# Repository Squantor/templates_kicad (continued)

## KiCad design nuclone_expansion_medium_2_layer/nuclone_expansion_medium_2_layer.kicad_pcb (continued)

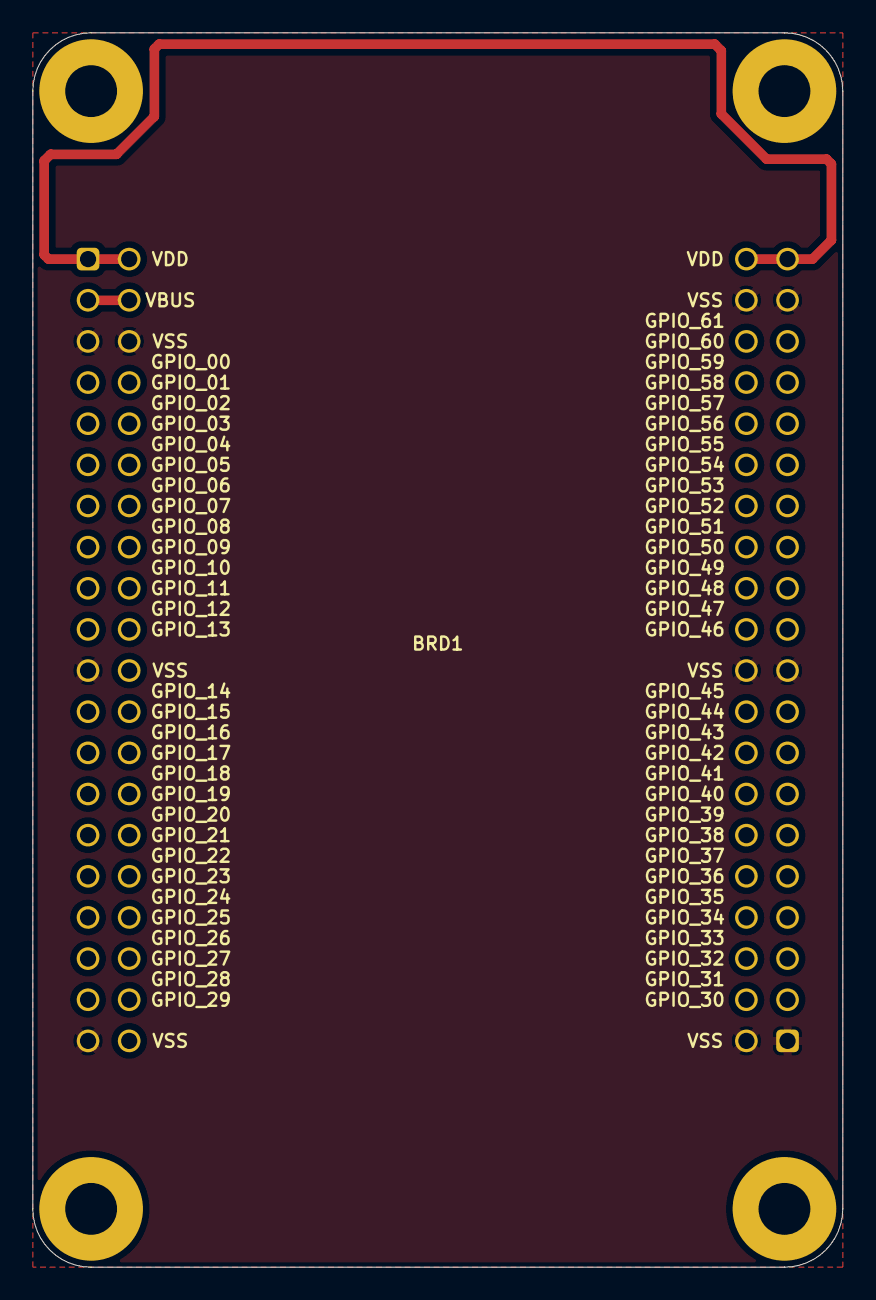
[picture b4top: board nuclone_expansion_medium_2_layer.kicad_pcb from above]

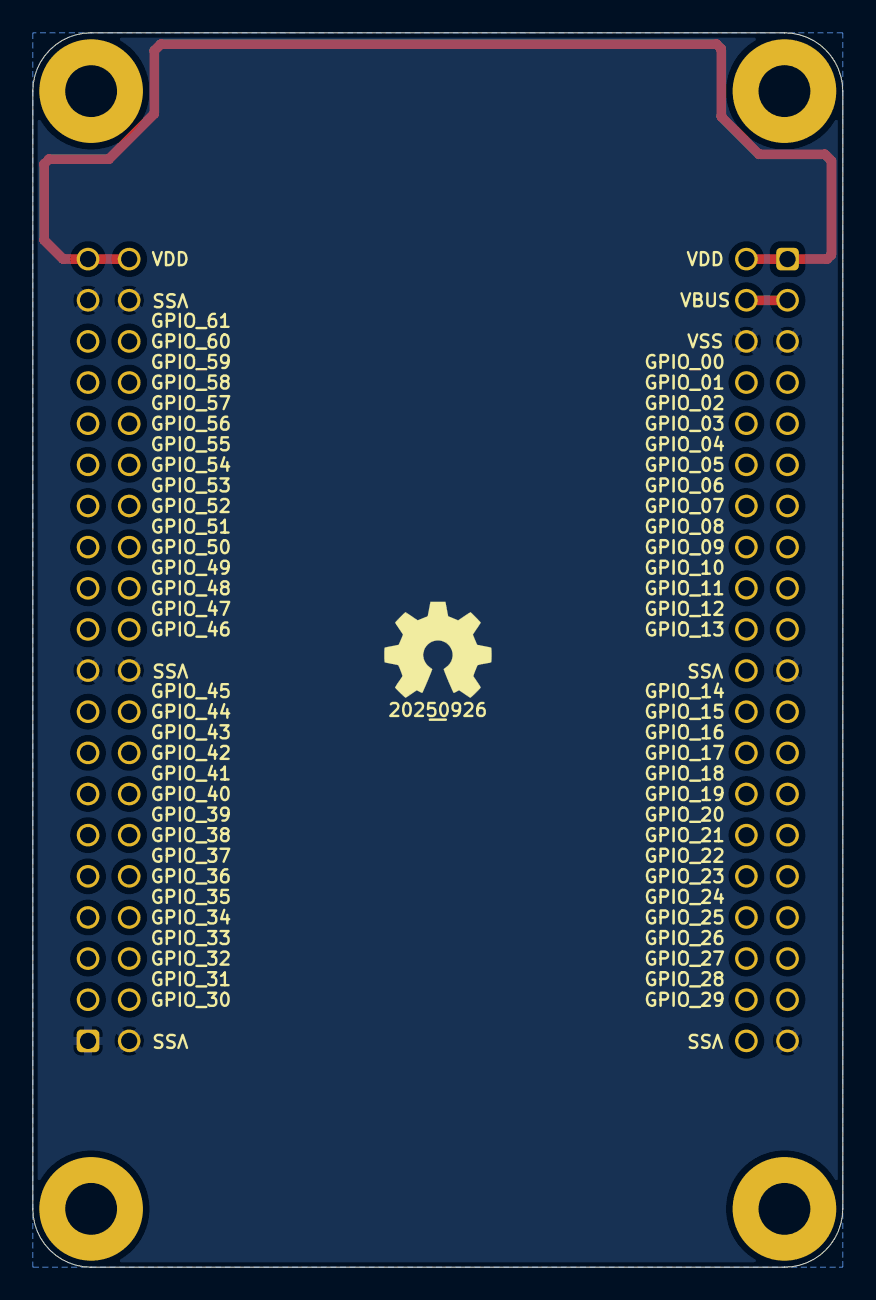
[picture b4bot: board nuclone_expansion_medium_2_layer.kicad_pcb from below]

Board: 2 copper layers, 50.0 x 76.2 mm, 3 parts (2 on the bottom side), 3 nets.

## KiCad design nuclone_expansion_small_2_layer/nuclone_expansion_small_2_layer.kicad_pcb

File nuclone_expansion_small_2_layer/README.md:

# Nuclone expansion board
Nuclone expansion board
# HSI (Hardware Software Interface)
This applies to a project that has a embedded software component. Describe what each pin/bus does, what it is connected to, what its function is and some "safe" behaviour when starting up.
## TODO's
Still some things need to be done:
* Fill in this project description
* schematic entry 
* PCB layout
* Review with one night in between
* Produce at [Aisler](https://aisler.net/)
* Assemble
* Test & characterise
* update Readme.md with pictures and BOM
## BOM
This is a list of hardware components. If just mentioned a generic component like a 1K 0402 resistor, just name it as such, free to substitute. If you need some special integrated IC's show some sources like Mouser, Digikey, Farnell, or LCSC
* Generic resistor in 0402 housing with a value
* Generic capacitor in 0603 housing with a value
* Special IC from [LCSC](https://lcsc.com/)
## Pictures

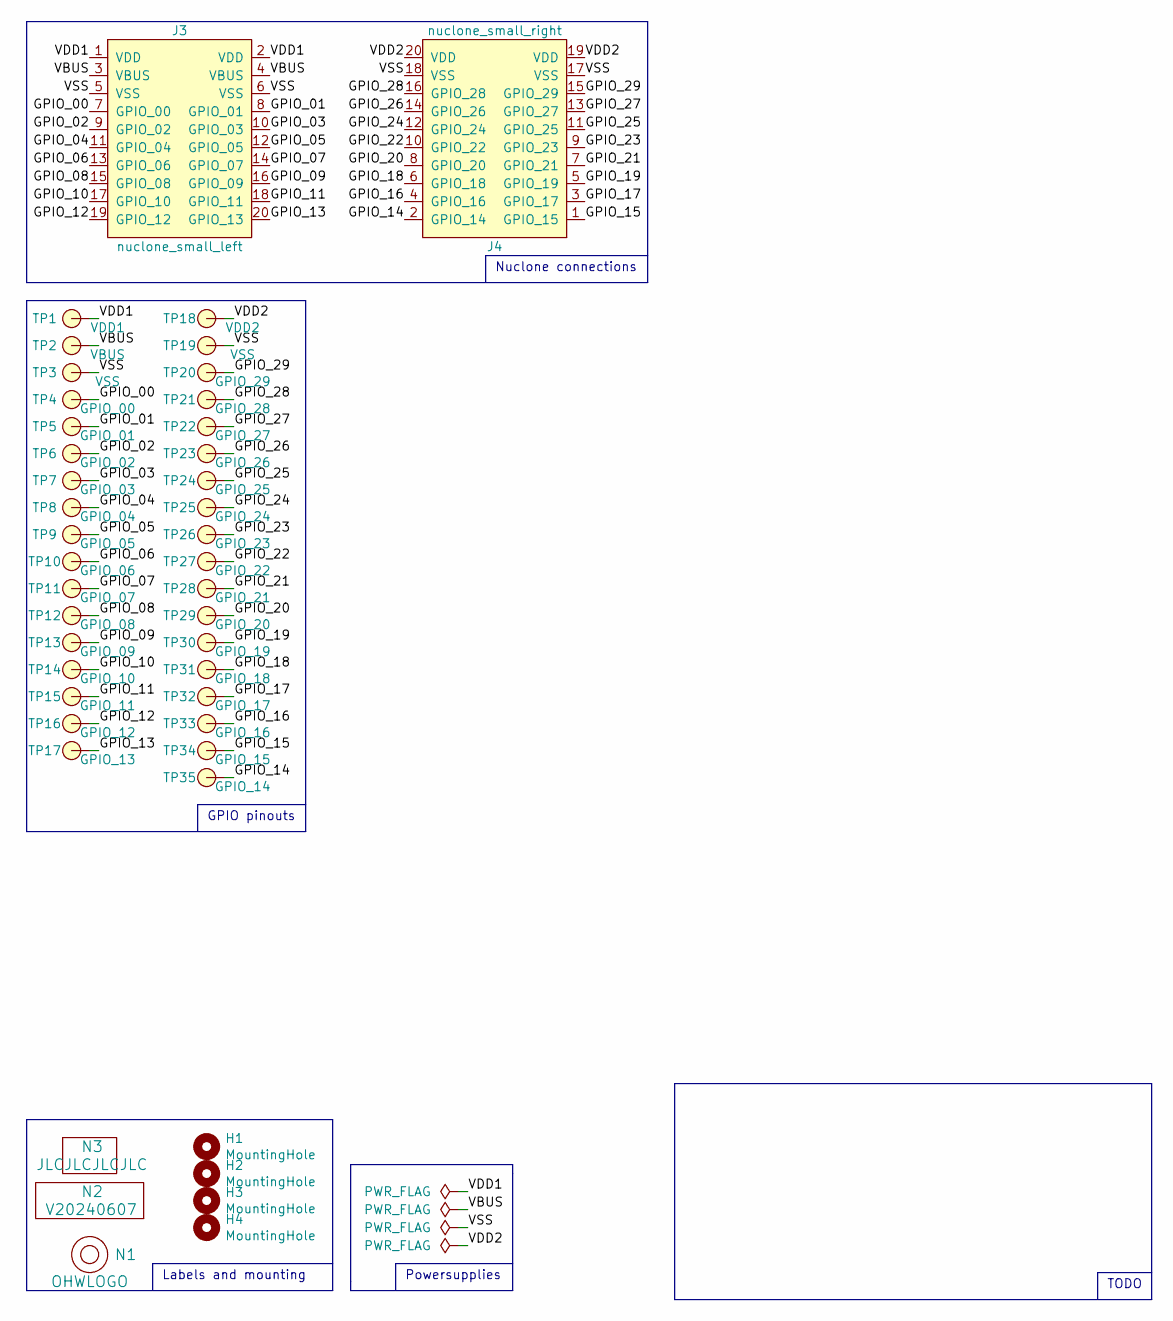
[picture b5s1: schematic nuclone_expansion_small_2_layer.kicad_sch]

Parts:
H1, H2, H3, H4: MountingHole; MountingHole_3.2mm_M3_Pad_Via
J3: nuclone_small_left; nuclone_small_left_stacked
J4: nuclone_small_right; nuclone_small_right_stacked
N1: OHWLOGO; OSHW-Symbol_6.7x6mm_SilkScreen
N2: V20240607; Label_Generic
N3: JLCJLCJLCJLC; Label_Generic
TP1: VDD1; TestPoint_hole_H05R10_2side
TP2: VBUS; TestPoint_hole_H05R10_2side
TP3, TP19: VSS; TestPoint_hole_H05R10_2side
TP4: GPIO_00; TestPoint_hole_H05R10_2side
TP5: GPIO_01; TestPoint_hole_H05R10_2side
TP6: GPIO_02; TestPoint_hole_H05R10_2side
TP7: GPIO_03; TestPoint_hole_H05R10_2side
TP8: GPIO_04; TestPoint_hole_H05R10_2side
TP9: GPIO_05; TestPoint_hole_H05R10_2side
TP10: GPIO_06; TestPoint_hole_H05R10_2side
TP11: GPIO_07; TestPoint_hole_H05R10_2side
TP12: GPIO_08; TestPoint_hole_H05R10_2side
TP13: GPIO_09; TestPoint_hole_H05R10_2side
TP14: GPIO_10; TestPoint_hole_H05R10_2side
TP15: GPIO_11; TestPoint_hole_H05R10_2side
TP16: GPIO_12; TestPoint_hole_H05R10_2side
TP17: GPIO_13; TestPoint_hole_H05R10_2side
TP18: VDD2; TestPoint_hole_H05R10_2side
TP20: GPIO_29; TestPoint_hole_H05R10_2side
TP21: GPIO_28; TestPoint_hole_H05R10_2side
TP22: GPIO_27; TestPoint_hole_H05R10_2side
TP23: GPIO_26; TestPoint_hole_H05R10_2side
TP24: GPIO_25; TestPoint_hole_H05R10_2side
TP25: GPIO_24; TestPoint_hole_H05R10_2side
TP26: GPIO_23; TestPoint_hole_H05R10_2side
TP27: GPIO_22; TestPoint_hole_H05R10_2side
TP28: GPIO_21; TestPoint_hole_H05R10_2side
TP29: GPIO_20; TestPoint_hole_H05R10_2side
TP30: GPIO_19; TestPoint_hole_H05R10_2side
TP31: GPIO_18; TestPoint_hole_H05R10_2side
TP32: GPIO_17; TestPoint_hole_H05R10_2side
TP33: GPIO_16; TestPoint_hole_H05R10_2side
TP34: GPIO_15; TestPoint_hole_H05R10_2side
TP35: GPIO_14; TestPoint_hole_H05R10_2side

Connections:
/GPIO_00: J3.7 (GPIO_00), TP4.1
/GPIO_01: J3.8 (GPIO_01), TP5.1
/GPIO_02: J3.9 (GPIO_02), TP6.1
/GPIO_03: J3.10 (GPIO_03), TP7.1
/GPIO_04: J3.11 (GPIO_04), TP8.1
/GPIO_05: J3.12 (GPIO_05), TP9.1
/GPIO_06: J3.13 (GPIO_06), TP10.1
/GPIO_07: J3.14 (GPIO_07), TP11.1
/GPIO_08: J3.15 (GPIO_08), TP12.1
/GPIO_09: J3.16 (GPIO_09), TP13.1
/GPIO_10: J3.17 (GPIO_10), TP14.1
/GPIO_11: J3.18 (GPIO_11), TP15.1
/GPIO_12: J3.19 (GPIO_12), TP16.1
/GPIO_13: J3.20 (GPIO_13), TP17.1
/GPIO_14: J4.2 (GPIO_14), TP35.1
/GPIO_15: J4.1 (GPIO_15), TP34.1
/GPIO_16: J4.4 (GPIO_16), TP33.1
/GPIO_17: J4.3 (GPIO_17), TP32.1
/GPIO_18: J4.6 (GPIO_18), TP31.1
/GPIO_19: J4.5 (GPIO_19), TP30.1
/GPIO_20: J4.8 (GPIO_20), TP29.1
/GPIO_21: J4.7 (GPIO_21), TP28.1
/GPIO_22: J4.10 (GPIO_22), TP27.1
/GPIO_23: J4.9 (GPIO_23), TP26.1
/GPIO_24: J4.12 (GPIO_24), TP25.1
/GPIO_25: J4.11 (GPIO_25), TP24.1
/GPIO_26: J4.14 (GPIO_26), TP23.1
/GPIO_27: J4.13 (GPIO_27), TP22.1
/GPIO_28: J4.16 (GPIO_28), TP21.1
/GPIO_29: J4.15 (GPIO_29), TP20.1
/VBUS: J3.3 (VBUS), J3.4 (VBUS), TP2.1
/VDD1: J3.1 (VDD), J3.2 (VDD), TP1.1
/VDD2: J4.19 (VDD), J4.20 (VDD), TP18.1
/VSS: J3.5 (VSS), J3.6 (VSS), J4.17 (VSS), J4.18 (VSS), TP3.1, TP19.1

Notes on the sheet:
Nuclone connections
TODO
Labels and mounting
Powersupplies
GPIO pinouts

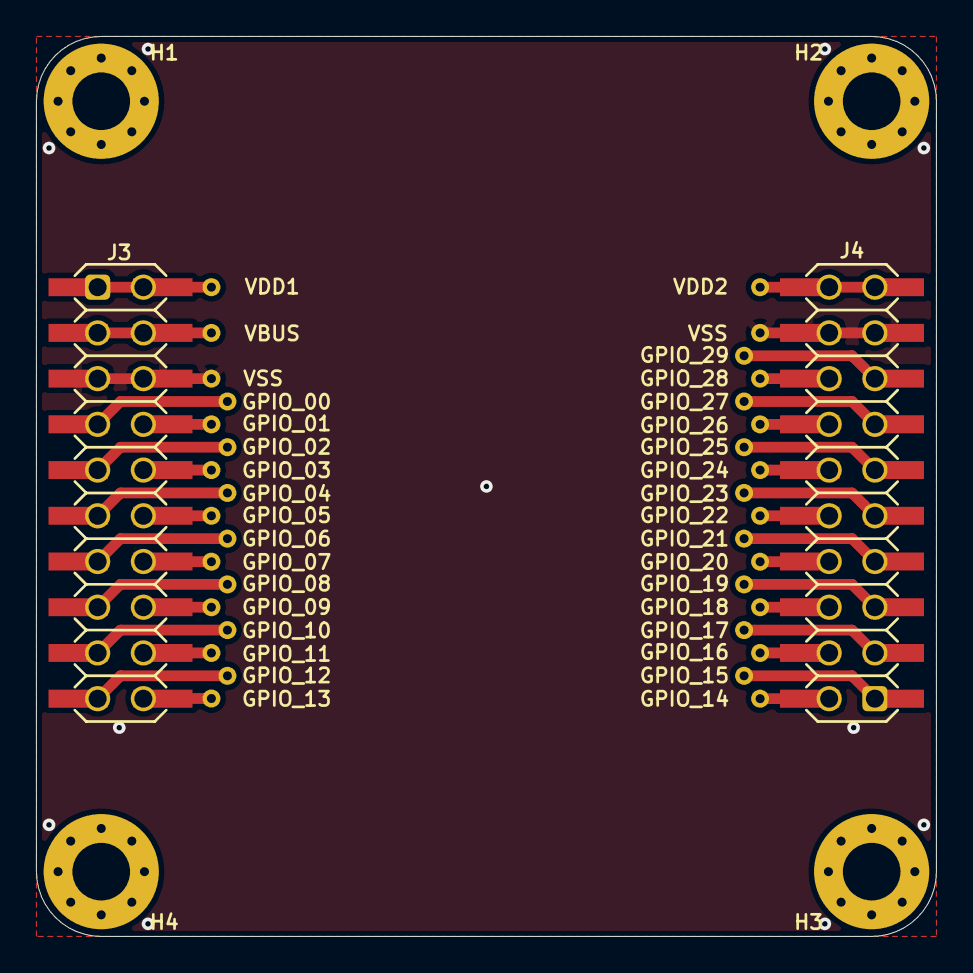
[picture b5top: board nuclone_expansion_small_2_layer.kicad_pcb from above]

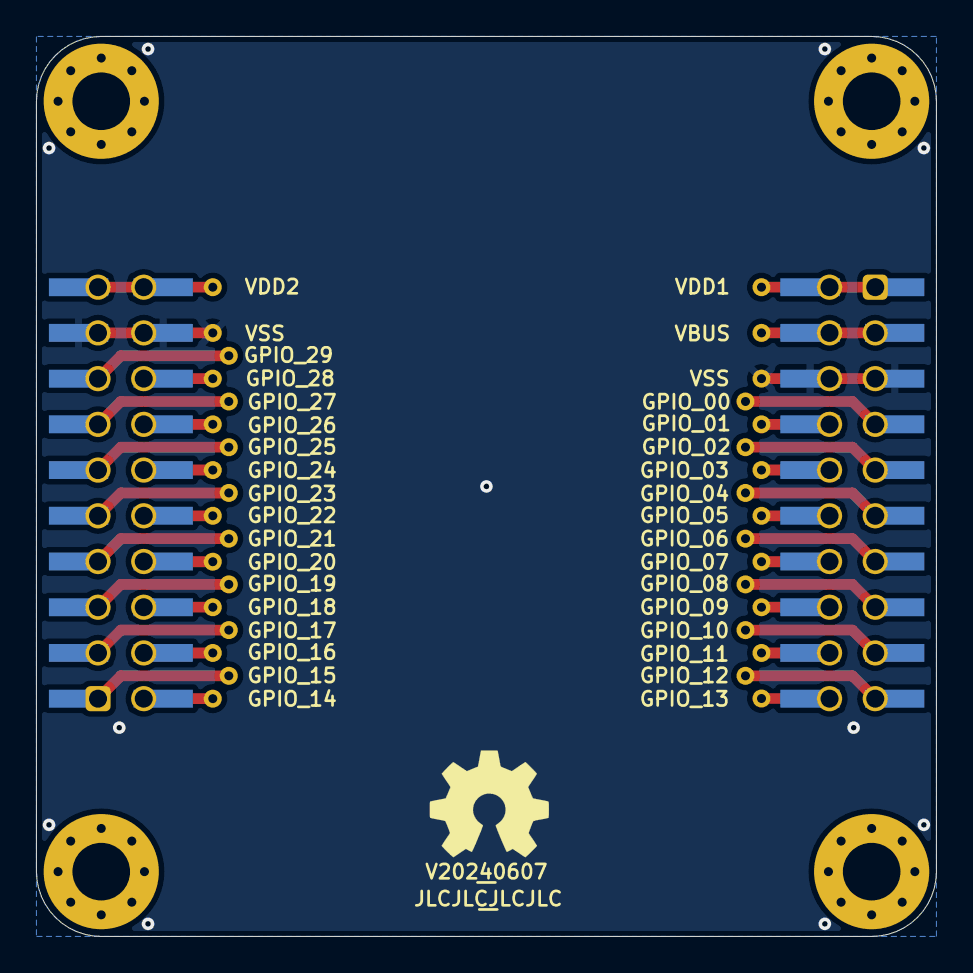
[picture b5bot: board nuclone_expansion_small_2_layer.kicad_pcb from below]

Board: 2 copper layers, 50.0 x 50.0 mm, 44 parts (3 on the bottom side), 34 nets.

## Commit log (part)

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2018-07-26 conversion to kicad 5
2018-07-26 updated JLCPCB 2layer template to kicad 5
2018-07-26 converted 4 layer JLCPCB template to kicad 5
2018-07-26 forgot symbol table
2018-07-26 updated Hammond 1593K JLCPCB 2 layer template
2018-07-26 updated Hammond 1551G JLCPCB 4 layer central devkit template
2018-08-19 added straggling file
2018-08-19 added nickel beetle 4 layer template
2018-08-19 updated Nickel beetle template project
2018-08-19 rename action of files
2018-09-10 updated OSH park 2 layer template
2018-09-10 added 4 layer OSH Park template
2018-11-08 updated OSH-park 2 layer template
2018-11-08 updated readme with submodule manual
2018-11-08 updated 4 layer oshpark template with project relative paths
2018-11-08 added all libraries, delete them when not needed, okay?
2018-11-13 added readme file examples to the templates
2018-11-13 added updated lib
2018-11-13 updated readme template, still todo all the other templates
2018-11-22 enlarged via annular ring defaults
2018-11-22 updated via sizes, updated layers, updated plotting settings
2018-11-24 added generate gerber scripts copied from splitflap
2018-12-08 added kicad template meta dir for hammond 1551G JLCPCB4 template
2018-12-08 ignoring rescue dirs
2018-12-15 updated pcb library
2019-01-22 updated hammond 4 layer oshpark central template
2019-01-22 updated Hammond 1550Z113 template with newer project version
2019-01-23 small update on 2 layer OSH park template
2019-01-23 updated hammond 1551G oshpark 2 layer template
2019-01-23 added Hammond 1551G OSHpark 2 layer devboard template
2019-01-23 renamed dir
2019-01-23 renamed files, updated soldermask clearances
2019-01-23 added 4layer devboard
2019-01-23 added proper template description
2019-01-24 updated to newer pcb library
2019-01-24 updated devboard pinout
2019-03-08 updated library
2019-03-08 fixed errors in descriptions and consistencies
2019-03-11 updated pcb component library to newest version
2019-03-13 updated paste vs pad ratio, updated soldermask clearance
2019-03-20 newer library version
2019-03-20 added one square inch 2 layer template
2019-04-07 added new libraries to templates
2019-04-12 added named connectors and fixed a flaw in paths
2019-05-20 updated Hammond 1551M template
2019-06-06 updated removal of NXP library
2019-07-04 updated solderpaste expansion to 0%
2019-07-05 fixed invalid symbol
2019-08-07 ignoring caches
2019-08-07 added meta files
2019-08-07 added pcb outlines, still need to check if it is the actual size
2019-08-09 updated alttext of template info
2019-08-27 added readmes to jlcpcb templates
2019-10-04 added updated pcb library
2019-10-04 added all resistors
2019-10-04 fixed ERC errors
2019-10-04 initial component placement
2019-10-04 some more routing improvements
2019-10-04 updated versionnumber
2019-10-06 aligned groundplane better
2019-10-06 cleaned up expansion board
2019-10-06 updated small nuclone expansion board template
2019-10-11 shrunk pcb, added keepout zones and initial nets
2020-01-03 fixed error when having the PCB library in the templates directory
2020-01-04 removed defunct button symbol library
2020-05-13 updated symbol and footprint libraries
2020-06-10 started new Oshpark 2 layer template conforming to newer kicad file format
2020-06-10 added version number and OHW logo
2020-06-10 added versionnumber and logo
2020-06-10 added trace and via classes
2020-06-10 removed older version of 2 layer oshpark template
2020-06-10 why did I even have this, it is just the osh 2 layer with a 1 inch board outline, that is like 15 seconds of work
2020-08-05 WIP small nuclone expansion board
2020-08-05 newer pcb library
2020-08-07 added newer header from pcb library, footprints connected on nuclone small expansion
2020-08-08 changed default font size, added pin labels
2020-08-08 renamed small nuclone templates
2020-08-08 renamed the project files too
2020-08-08 added shrunk version of small nuclone expansion shield
2020-08-08 adjusted board outline a bit to make it two square inches
2020-08-08 updated documentation with better wording
2020-09-10 added small nuclone expansion for the LPC824M201JHI33 nuclone
2020-09-16 updated to newest PCB library
2020-11-03 updated and adapted some new nets
2020-11-03 updated labels
2020-11-03 made description a bit more clear and consistent
2020-11-08 named pin nets
2020-11-08 moved around things
2020-11-08 updated library tables
2020-11-09 removed old components, started initial placement
2020-11-09 routed JTAG
2020-11-09 updated medium sized nuclone connector
2020-11-10 updated to newer medium sized nuclone boards
2020-11-10 updated header footprints
2020-11-10 silk improvements
2020-11-14 copied over medium nuclone to small nuclone board
2020-11-15 switched connectors
2020-11-15 resized the small nuclone board
2020-11-15 added schematic part names
2020-11-15 rounded the PCB corners a bit more
2020-11-15 updated versionnumber, added nuclone title
2021-03-14 added silergy and diodes inc schematic parts
2021-03-17 tired of manually synchronising tables when I introduce a new library
2021-03-17 added phoenix contact footprint library
2021-04-30 created template for Aisler simple profile
2021-04-30 update PCB library
2021-08-19 updated submodule URL
2021-08-19 updated medium nuclone devboard template
2021-08-19 WIP hierarchical subdivision of medium sized nuclone devboard, added some improvements to the medium size nuclone board template
2021-08-29 WIP schematic layout
2021-08-29 fixed and updated PCB library
2021-08-29 updated template schematic to pass ERC
2021-08-31 small updates
2021-08-31 updated small nuclone PCB
2021-08-31 with updated versionnumber
2021-09-13 fixed invalid path in footprint tables
2021-09-21 adjusted edges of medium nuclones
2021-10-15 forgotten one template
2021-10-29 changed USB routing
2021-10-29 changed groundplane of voltage regulator
2021-10-29 updated html documentation to correctly reflect template state
2021-11-07 changed small nuclone layout
2021-11-07 matchin small and medium nuclone boards with eachother
2021-11-09 added nuclone template versionnumber
2021-11-19 started in changing nuclone with smd headers
2021-11-19 WIP modifying medium nuclone to have stacked headers
2021-11-19 added PCB library
2021-11-21 updated planes and minor routing
2021-11-23 small routing improvements
2021-11-24 updated nuclone templates
2022-02-13 WIP mechanical outline
2022-02-14 added ESD protection diodes to USB
2022-02-14 placed, routed usb ESD diode
2022-02-14 rename actions
2022-02-14 added 4 layer nuclone template
2022-02-15 rename action for nuclone expansion
2022-02-15 updated small nuclone expansion board template with new mechanical outline
2022-02-15 started with first breakout testpoints
2022-02-15 routed left testpoints
2022-02-15 added left side connector test points
2022-02-17 added documentation block for the breakout of testpads
2022-02-17 started with template for small nuclone expansion with USB to serial converter, prototyping area and some connectors
2022-02-18 removed defunct file
2022-02-18 updated to have proper fuse footprint
2022-02-18 added usb input circuitry
2022-02-18 added usb2serial, routing in progress
2022-02-18 further layout and placement
2022-02-20 Added breakout connection and prototyping area
2022-02-20 updated prototyping area
2022-02-21 updated prototyping libs
2022-02-21 updated footprints for prototyping area
2022-02-21 changed pin labels
2022-05-06 updated to kicad6 component library
2022-05-06 WIP: conversion to kicad 6
2022-05-06 updated project to kicad 6
2022-05-06 updated blank template information
2022-05-06 forgotten some text
2022-05-06 updated jlcpcb 4 layer template to kicad6
2022-05-06 updated pcb design rules
2022-05-06 updated initial template
2022-05-11 updated to kicad 6 format
2022-05-11 conversion to kicad 6
2022-05-11 conversion to kicad6
2022-05-13 prettyfied the small nuclone expansion
2022-05-13 updated versionnumber, placed labels
2022-05-13 updated pads
2022-05-30 removing defunct projects
2022-05-30 added raspberry pi library
2022-05-30 small schematic changes and updated versionnumber
2022-05-30 changed copper zone with proper priorities
2022-05-30 fixed changed openhardware logo footprint
2022-05-30 changed via sizes to conform
2022-06-26 adding plot generation stuff to gitignore
2022-06-26 fixed typo in footprint table
2022-06-26 fixed typo in fp lib tables
2022-08-26 fixed via sizes in templates
2023-04-21 added few default nets
2023-04-21 created alubox 10x10 1x1 module template
2023-04-23 templated the 10x10cm alu box backplane
2023-04-23 templated 10x10 cm module 1x2
2023-06-19 updated description
2023-06-23 updated to converted libraries
2023-06-23 renaming 10x10 alubox pcb
2023-06-23 updated minimal 10x10 alubox template
2023-07-14 updated to kicad 7
2023-07-14 added kicad temporary
2023-07-14 project update
2023-07-14 updated, placed and routed reduced part sets
2023-07-14 small trace updates
2023-07-14 updated template readme
2023-10-04 updated board rules to conform to aisler simple
2023-10-06 updated UART proto with new header sizes
2023-12-14 synchronized aisler simple 2 layer
2023-12-14 updated copy tables with new templates and ordered by name
2023-12-14 added smaller vias and tracks to templates
2023-12-31 WIP DIN41612 3*10 connector backplane
2023-12-31 WIP routing backplane
2024-01-01 completed ModEleSys backplane based on DIN41612 connectors
2024-01-02 added power LED's
2024-01-02 adjusting mechanical dimensions to be more in line with ModEleSys V2.0
2024-01-02 updated ERC/DRC rules to match aisler
2024-01-03 ignoring some DRC warnings
2024-01-03 imported aisler simple design rules
2024-01-04 renamed some projects
2024-01-04 added additional projects/libraries
2024-01-04 renamed a library
2024-01-04 fixed description
2024-01-04 moved RLC parts to different libraries, fixed DRC errors, minor silk movements
2024-01-07 updated PCB library with newer fonts etc
2024-01-07 updated all footprints, routed and placed, fixed DRC/ERC
2024-01-09 updated to new components
2024-01-11 updated with ground pads
2024-01-12 small modifications
2024-01-12 minor silk movements, regulator more cooling
2024-01-14 updated versionnumbers
2024-01-23 WIP redoing the template
2024-01-24 renamed medium nuclone 2 layer board
2024-01-24 copy tables updated with new project
2024-01-24 completed medium nuclone with USB-C PD connector
2024-01-24 WIP rerouting board and making it common with the medium board
2024-01-25 P&R done, WIP placing silk items
2024-02-16 reviewed modelesys backplane
2024-02-18 preparing for production
2024-03-10 added diode in series
2024-03-10 added diode in USB power line
2024-03-10 adjusted diode position a bit
2024-03-10 fixed descriptions
2024-03-10 created initial SquMes-30 module template
2024-03-11 updated documentation
2024-03-11 WIP ModEleSys V2 1x1 module
2024-03-11 completed ModEleSys V2 1x2 sized module
2024-03-29 updated template values
2024-05-23 added new transistor schematic library
2024-06-05 rename
2024-06-05 moving board to uniform corner
2024-06-05 hole updates
2024-06-06 fixed alignment and positions
2024-06-06 small alignment and added vias
2024-06-06 updated boards
2024-06-06 added new small nuclone template with USB-C PD only
2024-06-07 updated description files
2024-06-09 updated silkscreen
2024-06-24 added gpio pin nets
2024-07-17 updated and fixed DRC/ERC warnings
2024-08-02 added some china protoboard templates
2025-07-29 Kicad template updates
2025-09-26 updated using board outline footprint
2025-09-26 switching from Oshpark to Aisler description
2025-09-26 Added nuclone medium expansion 2 layer template
2025-10-03 added new libraries and update tables, added medium nuclone with USB connection
2025-10-04 updated medium nuclone footprint in templates, updated library
2025-10-04 new kicad version
2025-10-15 updated to newer kicad version
